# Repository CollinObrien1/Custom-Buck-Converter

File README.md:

This is a repository for our Buck Converter Preliminary Design for ELEC 4450: Power Electronics.

The most up-to-date version of the PCB as of 2025-03-02 is: Buck_PCB- R3.0

EDA Models can be found in the folder: EDA Models

Thank you,

Gavin F., Collin O., Sahana J.

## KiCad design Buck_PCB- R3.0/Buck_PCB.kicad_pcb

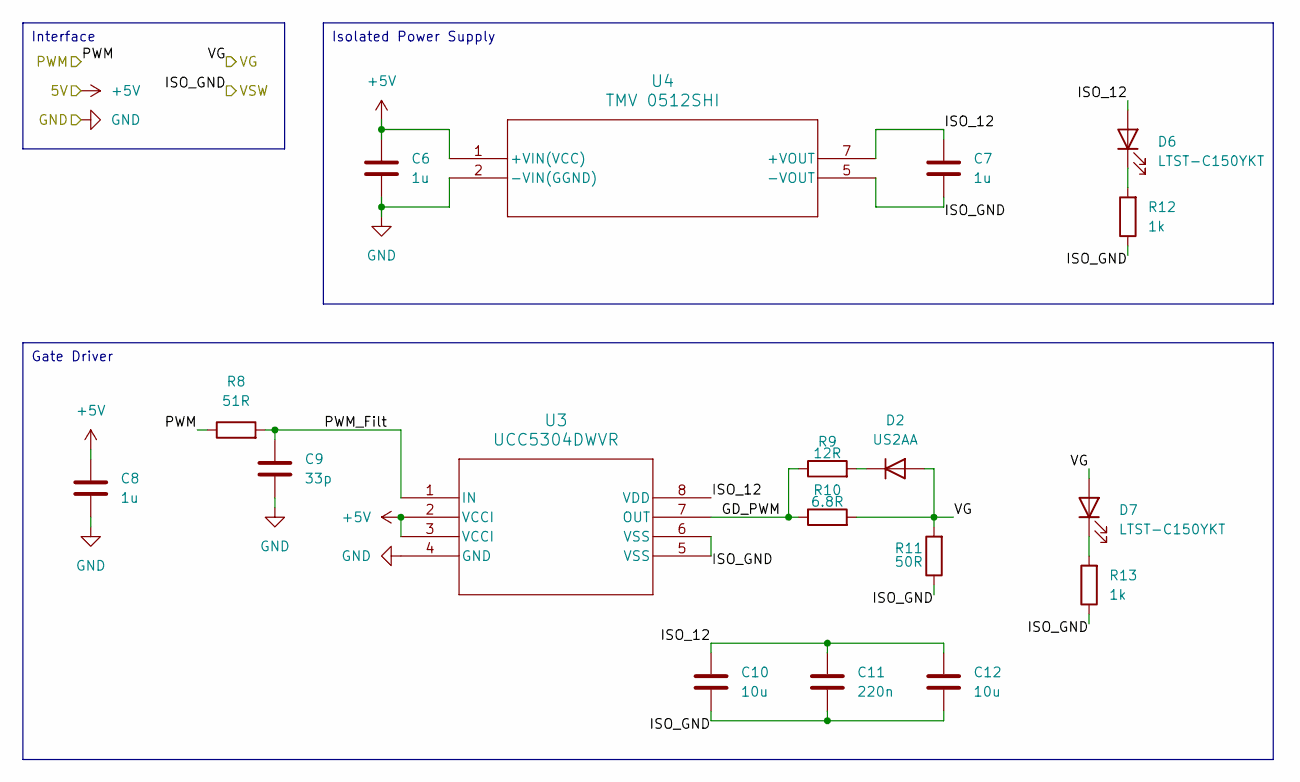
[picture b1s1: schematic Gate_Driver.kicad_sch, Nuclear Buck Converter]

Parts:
C6, C7, C8: 1u; C_0805_2012Metric_Pad1.18x1.45mm_HandSolder; Part Number TMCP1D105MTRF
C9: 33p; C_0805_2012Metric_Pad1.18x1.45mm_HandSolder; Part Number C0805C330J1GACTU
C10: 10u; C_0805_2012Metric_Pad1.18x1.45mm_HandSolder; Part Number F951C106MPAAQ2
C11: 220n; C_0805_2012Metric_Pad1.18x1.45mm_HandSolder; Part Number C0805C224K5RACTU
C12: 10u; C_0805_2012Metric_Pad1.18x1.45mm_HandSolder; Part Number GRM21BR61E106KA73L
D2: US2AA; D_SMA_Handsoldering; Part Number US2AA
D6, D7: LTST-C150YKT; LED_1206_3216Metric_Pad1.42x1.75mm_HandSolder; Part Number LTST-C150YKT
R8: 51R; R_0805_2012Metric_Pad1.20x1.40mm_HandSolder; Part Number RC0805FR-0751RL
R9: 12R; R_0805_2012Metric_Pad1.20x1.40mm_HandSolder; Part Number ERJ-P06J120V
R10: 6.8R; R_0805_2012Metric_Pad1.20x1.40mm_HandSolder; Part Number RCS08056R80FKEA
R11: 50R; R_1206_3216Metric_Pad1.30x1.75mm_HandSolder; Part Number RCP1206W50R0GEB
R12, R13: 1k; R_0805_2012Metric_Pad1.20x1.40mm_HandSolder; Part Number RMCF0805FT1K00
U3: UCC5304DWVR; SOIC8_DWV_TEX-L; Part Number UCC5304DWVR
U4: TMV 0512SHI; TMV-HI_SINGLE_TRP; Part Number TMV 0512SHI

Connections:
+5V: C6.2, C8.2, U3.2 (VCCI), U3.3 (VCCI), U4.1 (+VIN(VCC)); also elsewhere on the board
/GateDriver/GD_PWM: R9.1, R10.1, U3.7 (OUT)
/GateDriver/ISO_12: C7.2, C10.2, C11.2, C12.2, D6.2 (A), U3.8 (VDD), U4.7 (+VOUT)
/GateDriver/PWM_Filt: C9.1, R8.2, U3.1 (IN)
/PWM: R8.1; also elsewhere on the board
/VG: D2.2 (A), D7.2 (A), R10.2, R11.2; also elsewhere on the board
/VSW: C7.1, C10.1, C11.1, C12.1, R11.1, R12.1, R13.1, U3.5 (VSS), U3.6 (VSS), U4.5 (-VOUT); also elsewhere on the board
GND: C6.1, C8.1, C9.2, U3.4 (GND), U4.2 (-VIN(GGND)); also elsewhere on the board
unnamed: D2.1 (K), R9.2
unnamed: D6.1 (K), R12.2
unnamed: D7.1 (K), R13.2

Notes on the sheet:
Gate Driver
Isolated Power Supply
Interface

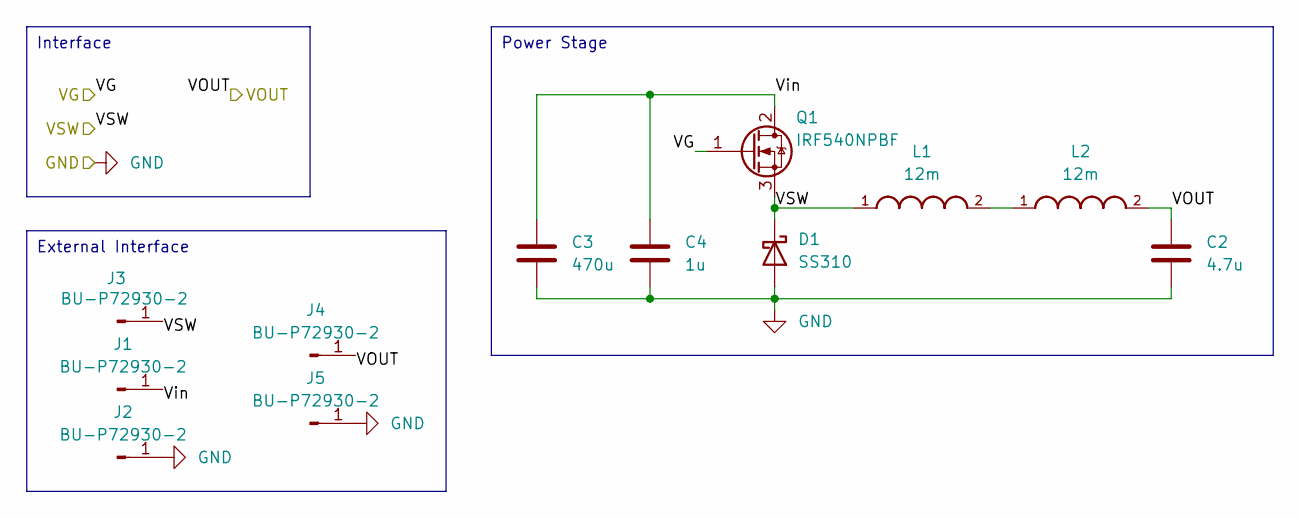
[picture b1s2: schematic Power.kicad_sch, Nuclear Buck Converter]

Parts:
C2: 4.7u; C_1206_3216Metric_Pad1.33x1.80mm_HandSolder; Part Number GRM31CC72A475KE11K
C3: 470u; CP_Radial_D18.0mm_P7.50mm; Part Number 100ZLH470MEFC16X31.5
C4: 1u; C_0805_2012Metric_Pad1.18x1.45mm_HandSolder; Part Number GRM21BC72A105KE01L
D1: SS310; D_SMA_Handsoldering; Part Number SS310
J1, J2, J3, J4, J5: BU-P72930-2; Banana_Jack_1Pin; Part Number BU-P72930-2
L1, L2: 12m; INDRD2921W163D3810H2616P; Part Number 1140-123K-RC
Q1: IRF540NPBF; TO-220-3_Vertical; Part Number IRF540NPBF

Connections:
/Power/Vin: C3.1, C4.1, J1.1, Q1.2 (D)
/VG: Q1.1 (G); also elsewhere on the board
/VOUT: C2.1, J4.1, L2.2; also elsewhere on the board
/VSW: D1.1 (K), J3.1, L1.1, Q1.3 (S); also elsewhere on the board
GND: C2.2, C3.2, C4.2, D1.2 (A), J2.1, J5.1; also elsewhere on the board
unnamed: L1.2, L2.1

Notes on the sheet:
Interface
Power Stage
External Interface

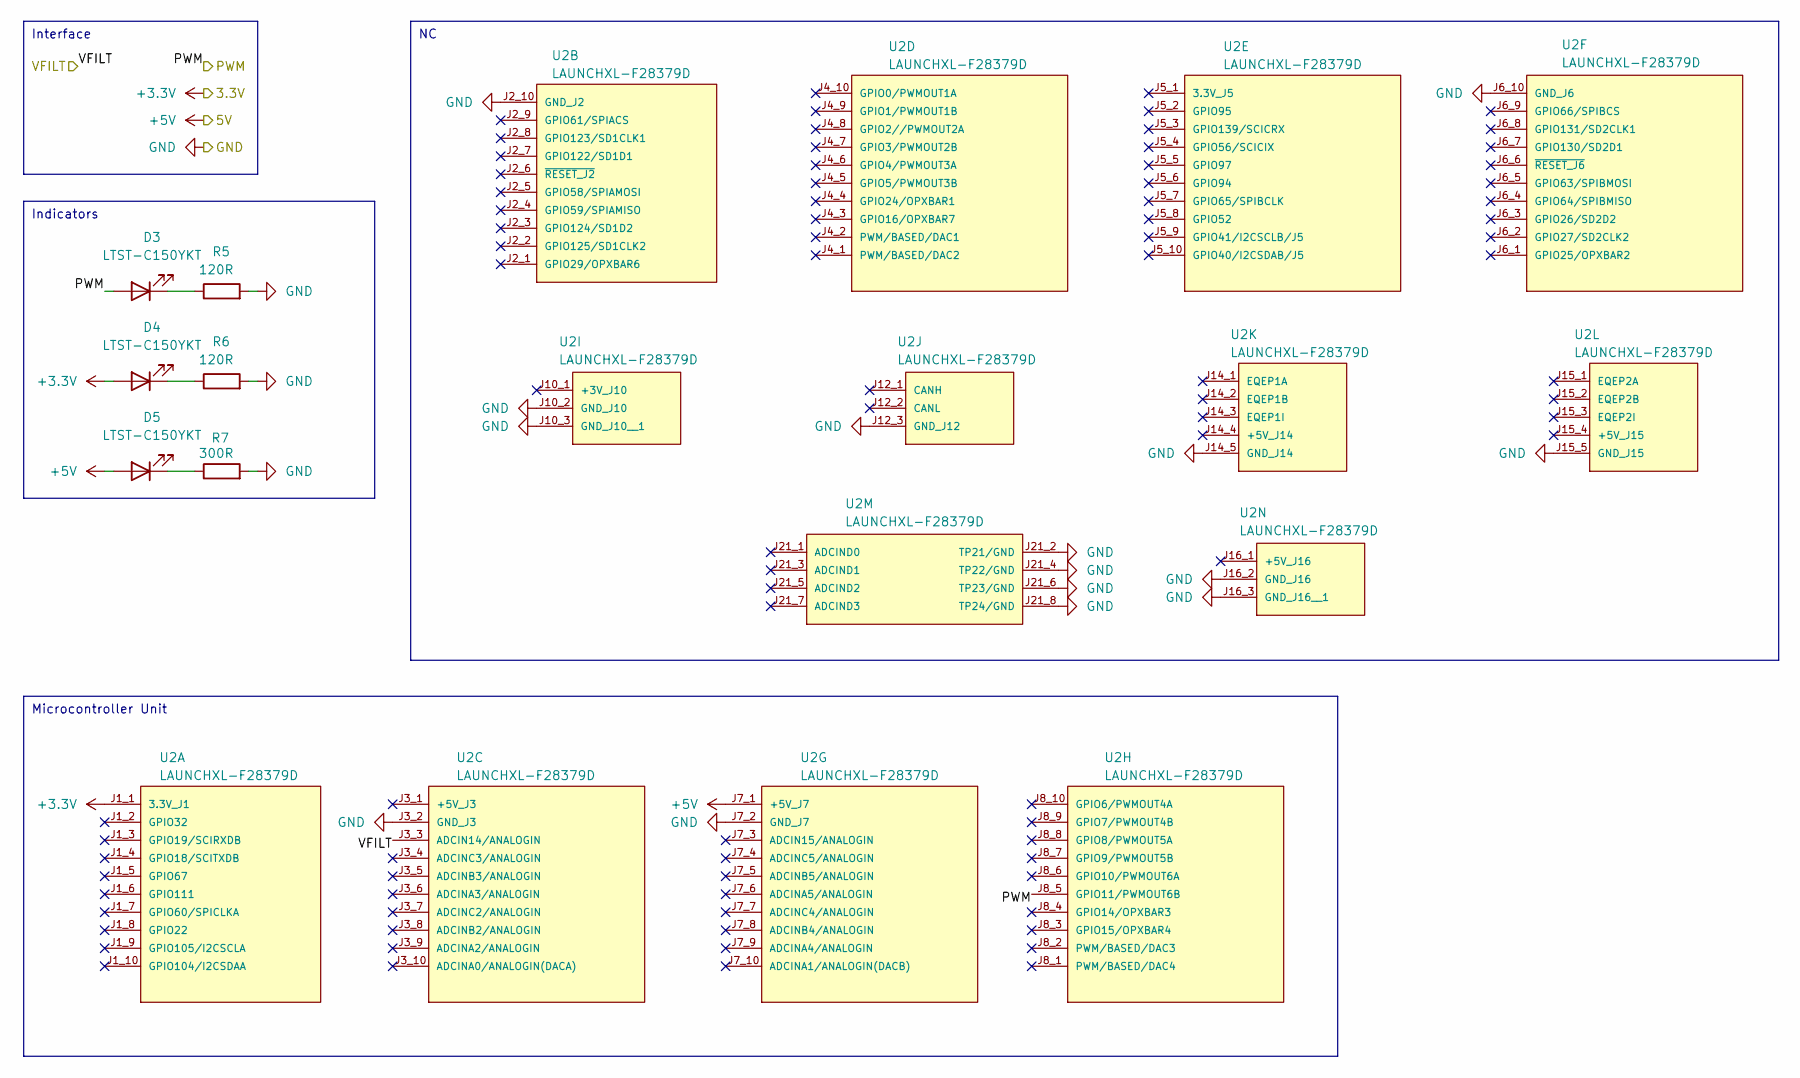
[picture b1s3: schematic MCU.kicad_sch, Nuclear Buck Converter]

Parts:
D3, D4, D5: LTST-C150YKT; LED_1206_3216Metric_Pad1.42x1.75mm_HandSolder; Part Number LTST-C150YKT
R5, R6: 120R; R_0805_2012Metric_Pad1.20x1.40mm_HandSolder; Part Number RMCF0805FT120R
R7: 300R; R_0805_2012Metric_Pad1.20x1.40mm_HandSolder; Part Number RMCF0805JT300R
U2: LAUNCHXL-F28379D; MOD_LAUNCHXL-F28379D; PARTREV 2.0

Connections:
+3.3V: D4.2 (A), U2.J1_1 (3.3V_J1); also elsewhere on the board
+5V: D5.2 (A), U2.J7_1 (+5V_J7); also elsewhere on the board
/PWM: D3.2 (A), U2.J8_5 (GPIO11/PWMOUT6B); also elsewhere on the board
/VFILT: U2.J3_3 (ADCIN14/ANALOGIN); also elsewhere on the board
GND: R5.2, R6.2, R7.2, U2.J2_10 (GND_J2), U2.J3_2 (GND_J3), U2.J6_10 (GND_J6), U2.J7_2 (GND_J7), U2.J10_2 (GND_J10), U2.J10_3 (GND_J10__1), U2.J12_3 (GND_J12), U2.J14_5 (GND_J14), U2.J15_5 (GND_J15), U2.J16_2 (GND_J16), U2.J16_3 (GND_J16__1), U2.J21_2 (TP21/GND), U2.J21_4 (TP22/GND), U2.J21_6 (TP23/GND), U2.J21_8 (TP24/GND); also elsewhere on the board
unnamed: D3.1 (K), R5.1
unnamed: D4.1 (K), R6.1
unnamed: D5.1 (K), R7.1

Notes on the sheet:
Indicators
Interface
Microcontroller Unit

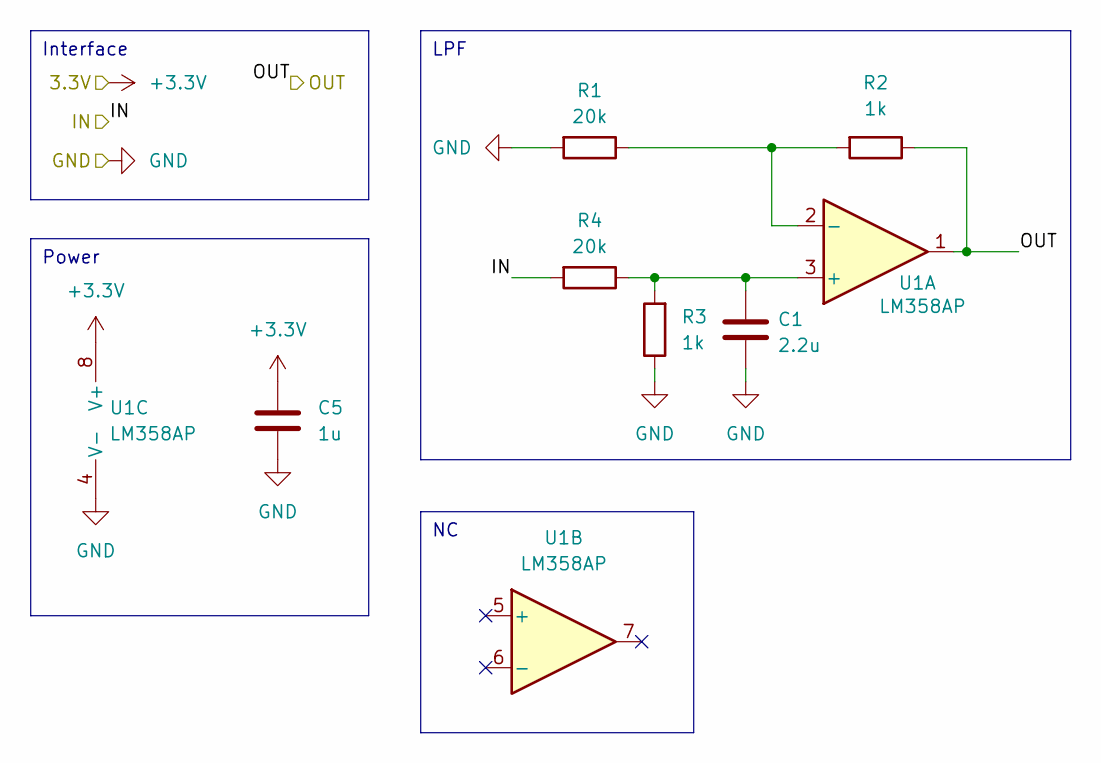
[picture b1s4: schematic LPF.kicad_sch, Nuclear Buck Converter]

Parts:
C1: 2.2u; C_0805_2012Metric_Pad1.18x1.45mm_HandSolder; Part Number CL21A225KBFNNNE
C5: 1u; C_0805_2012Metric_Pad1.18x1.45mm_HandSolder; Part Number TMCP1D105MTRF
R1, R4: 20k; R_0805_2012Metric_Pad1.20x1.40mm_HandSolder; Part Number RC0805FR-0720KL
R2, R3: 1k; R_0805_2012Metric_Pad1.20x1.40mm_HandSolder; Part Number RMCF0805FT1K00
U1: LM358AP; DIP794W45P254L959H508Q8; Part Number LM358AP

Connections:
+3.3V: C5.2, U1.8 (V+); also elsewhere on the board
/VFILT: R2.1, U1.1; also elsewhere on the board
/VOUT: R4.2; also elsewhere on the board
GND: C1.2, C5.1, R1.2, R3.1, U1.4 (V-); also elsewhere on the board
unnamed: C1.1, R3.2, R4.1, U1.3 (+)
unnamed: R1.1, R2.2, U1.2 (-)

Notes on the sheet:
Power
LPF
Interface

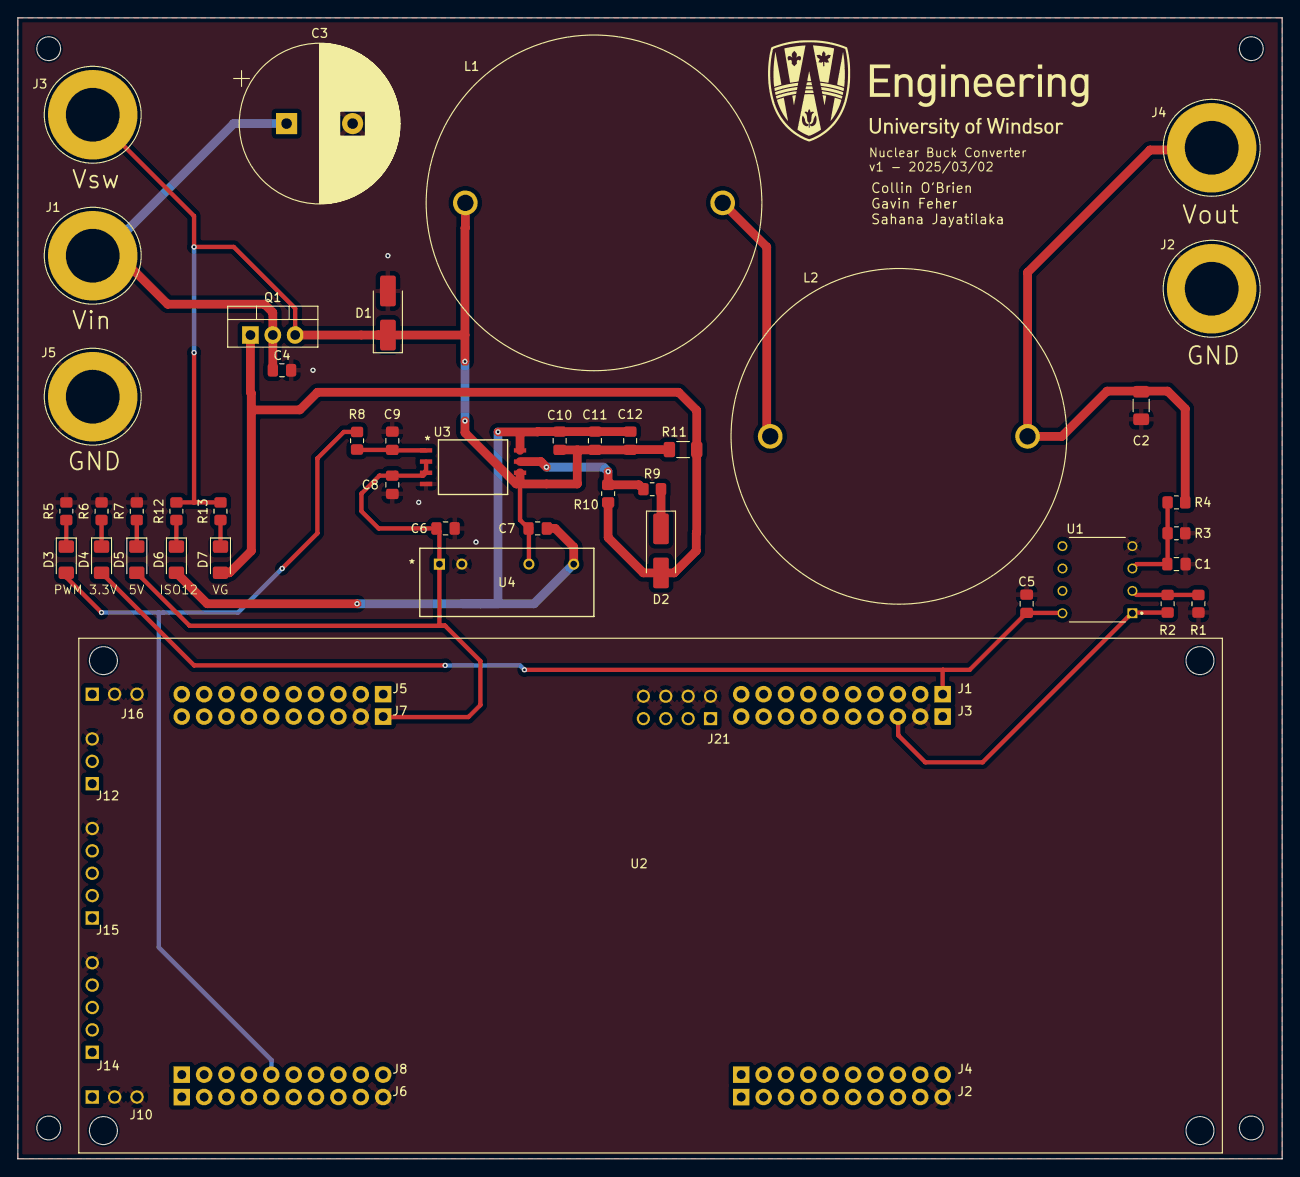
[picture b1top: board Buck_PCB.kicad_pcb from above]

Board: 2 copper layers, 143.5 x 129.5 mm, 44 parts (0 on the bottom side), 21 nets.

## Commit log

2025-02-20 Add files via upload
    R1.0 of buck boost project
2025-03-02 Create DigiKey_Cart
